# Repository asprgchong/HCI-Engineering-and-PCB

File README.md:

# HCI-Engineering-and-PCB
Project Files from my HCI PCB and HCI Eng classes with Professor Pedro Lopes

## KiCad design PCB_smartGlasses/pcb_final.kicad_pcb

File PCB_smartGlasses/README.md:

## PCB Smart Glasses Project: 
Final Project for HCI PCB with Prof Lopes result

This class was an amazing experience into the harsh world of EE and prototyping. 
My idea was to create smart glasses from scratch that a user would interact with using gestures and a smart glasses product that would also react to the user's environment. 
During the KiCAD wiring and organization process, I had messed up the wiring of the SCL and SDA pins on the wrong pins on the SAMD21 processor which was a TQFP component hot gun soldered down. As depicted above, there is a stray wire running to the VCC pin on my OLED.
There were a lot of things that went wrong with this project and hence it's roughness. But I'm really proud of this project! 

I had no prior experience and I made a fully functioning smart glasses product that allowed the user to see the to-do list. I don't have my glasses anymore, they are with Prof Lopez but I am actively working on my mistakes and trying to make it better.

<p>Components and Schematic Design (Problems in the wiring of the SLA and SCL of the light sensor to the correct pins on the SAMD21- same for the OLED screen)</p>

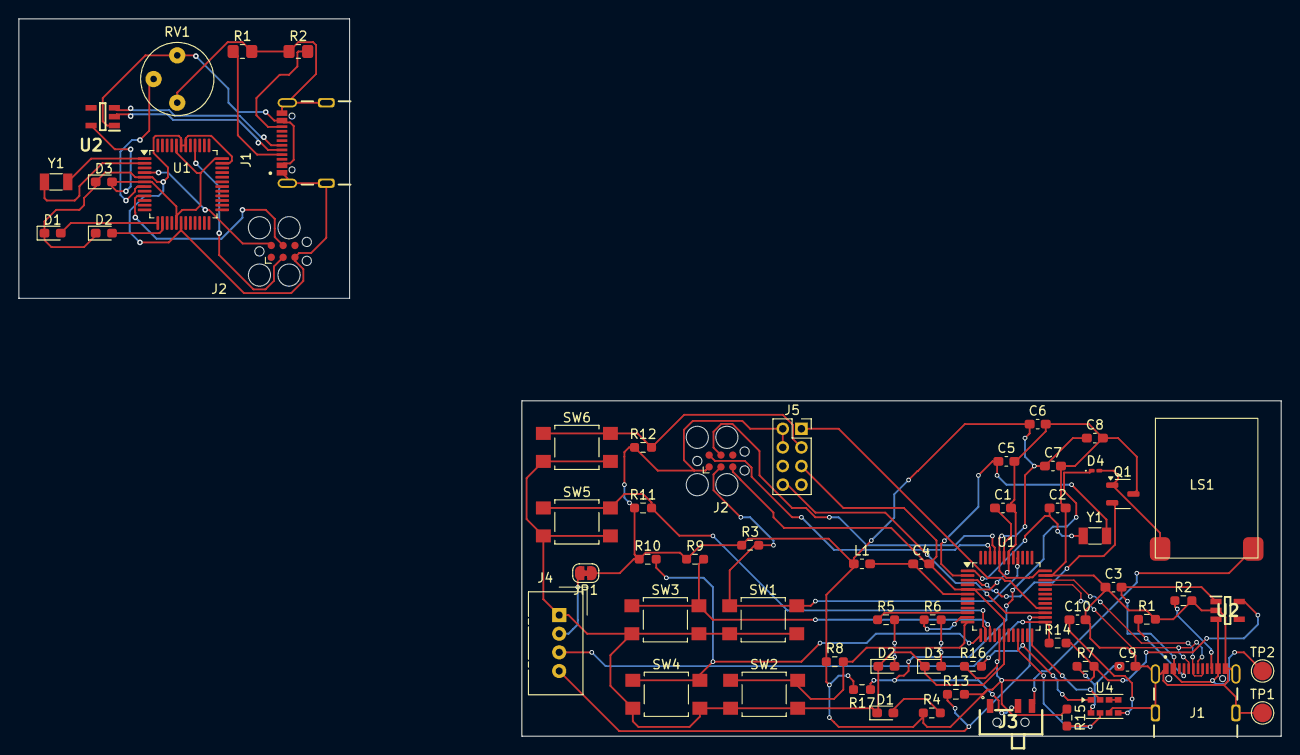
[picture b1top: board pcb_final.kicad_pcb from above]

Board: 2 copper layers, 135.5 x 77.0 mm, 63 parts (0 on the bottom side), 13 nets.

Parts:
C1, C4, C6, C7: 0.1uF; C_0603_1608Metric_Pad1.08x0.95mm_HandSolder
C2, C5: 15uF; C_0603_1608Metric_Pad1.08x0.95mm_HandSolder
C3, C8, C9, C10: 1uF; C_0603_1608Metric_Pad1.08x0.95mm_HandSolder
D1: GREEN; LED_0603_1608Metric_Pad1.05x0.95mm_HandSolder
D1#2, D2#2, D3: LED; LED_0603_1608Metric_Pad1.05x0.95mm_HandSolder
D2, D3#2: RED; LED_0603_1608Metric_Pad1.05x0.95mm_HandSolder
D4: LED_Small; D_0201_0603Metric_Pad0.64x0.40mm_HandSolder
J1, J1#2: USB4105-GF-A; GCT_USB4105-GF-A
J2: SWD_TAG-CONNECT; Tag-Connect_TC2030-IDC-FP_2x03_P1.27mm_Vertical
J2#2: TAG-CONNECT; Tag-Connect_TC2030-IDC-FP_2x03_P1.27mm_Vertical
J3: SSSS810701
J4: Conn_01x04_Socket; NS-Tech_Grove_1x04_P2mm_Vertical
J5: Conn_02x04_Top_Bottom; PinSocket_2x04_P2.00mm_Vertical
JP1: Jumper_2_Bridged; SolderJumper-2_P1.3mm_Bridged_RoundedPad1.0x1.5mm
L1: FB-30R; L_0603_1608Metric_Pad1.05x0.95mm_HandSolder
LS1: OWS-111535LA-8H
Q1: NMOS; SOT-23-3
R1, R2: 5.1k; R_0603_1608Metric_Pad0.98x0.95mm_HandSolder
R1#2, R2#2: 5.1k; R_0805_2012Metric_Pad1.20x1.40mm_HandSolder
R3, R8, R9, R10, R11, R12, R13, R14, R15, R16, R17: 10k; R_0603_1608Metric_Pad0.98x0.95mm_HandSolder
R4, R5, R6: 1k; R_0603_1608Metric_Pad0.98x0.95mm_HandSolder
R7: 22; R_0603_1608Metric_Pad0.98x0.95mm_HandSolder
RV1: R_Potentiometer; Potentiometer_Bourns_3339P_Vertical_HandSoldering
SW1, SW2, SW3, SW4, SW5, SW6: SW_Push; SW_SPST_TL3305A
TP1, TP2: GND_Test; TestPoint_Pad_D2.0mm
U1, U1#2: ATSAMD21G18A-A; TQFP-48_7x7mm_P0.5mm
U2, U2#2: TLV73333PQDBVRQ1; SOT95P280X145-5N
U4: APDS-9960; Avago_APDS-9960
Y1: Crystal_Small; Crystal_SMD_3215-2Pin_3.2x1.5mm
Y1#2: Crystal; Crystal_SMD_3215-2Pin_3.2x1.5mm

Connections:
+5V: J1.A4_B9 (VBUS), J1.B4_A9 (VBUS), RV1.3, U2#2.1 (IN)
/D+: J1.A6 (DP1), J1#2.A6 (DP1), J1#2.B6 (DP2), U1#2.34 (PA25), U2#2.3 (EN)
/D-: J1.B7 (DN2), J1#2.A7 (DN1), J1#2.B7 (DN2), U1#2.33 (PA24), U2#2.2 (GND)
/InCrystal: U1.1 (PA00), Y1#2.1
/OutCrystal: U1.2 (PA01), Y1#2.2
/SWC: J2.4 (SWCLK), J2#2.4 (SWCLK), U1.9 (PA04), U1#2.45 (PA30)
/SWD: J2.2 (SWDIO), J2#2.2 (SWDIO), U1.4 (PA03), U1#2.46 (PA31)
/ledOne: D1#2.2 (A), U1.13 (PA08)
/ledTwo: D2#2.2 (A), U1.14 (PA09)
/pot_pin: RV1.2, U1.7 (PB08)
/regV: D3.2 (A), J2#2.1 (Vref), U1.6 (VDDANA), U1.17 (VDDIO), U1.36 (VDDIO), U1.44 (VDDIN), U2#2.5 (OUT)
/~RST: J2.3 (~RST), J2#2.3 (~RST), R3.2, SW1.1, U1.40 (~RESET), U1#2.40 (~RESET)
GND: C1.2, C2.2, C3.1, C4.2, C5.2, C6.2, C7.2, C8.2, C9.2, C10.2, D1.1 (K), D1#2.1 (K), D2.1 (K), D2#2.1 (K), D3.1 (K), D3#2.1 (K), J1.A1_B12 (GND), J1.B1_A12 (GND), J1.SH1 (SHELL_GND), J1.SH2 (SHELL_GND), J1.SH3 (SHELL_GND), J1.SH4 (SHELL_GND), J1#2.A1_B12 (GND), J1#2.B1_A12 (GND), J1#2.SH1 (SHELL_GND), J1#2.SH2 (SHELL_GND), J1#2.SH3 (SHELL_GND), J1#2.SH4 (SHELL_GND), J2.5 (GND), J2#2.5 (GND), J4.1, J5.5, Q1.3 (S), R1.2, R1#2.2, R2.2, R2#2.1, RV1.1, SW1.2, SW2.2, SW3.2, SW4.2, SW5.2, SW6.2, TP1.1, U1.5 (GNDANA), U1.18 (GND), U1.35 (GND), U1.42 (GND), U1.43 (VDDCORE), U1#2.5 (GNDANA), U1#2.18 (GND), U1#2.35 (GND), U1#2.42 (GND), U2.2 (GND), U4.6 (GND)

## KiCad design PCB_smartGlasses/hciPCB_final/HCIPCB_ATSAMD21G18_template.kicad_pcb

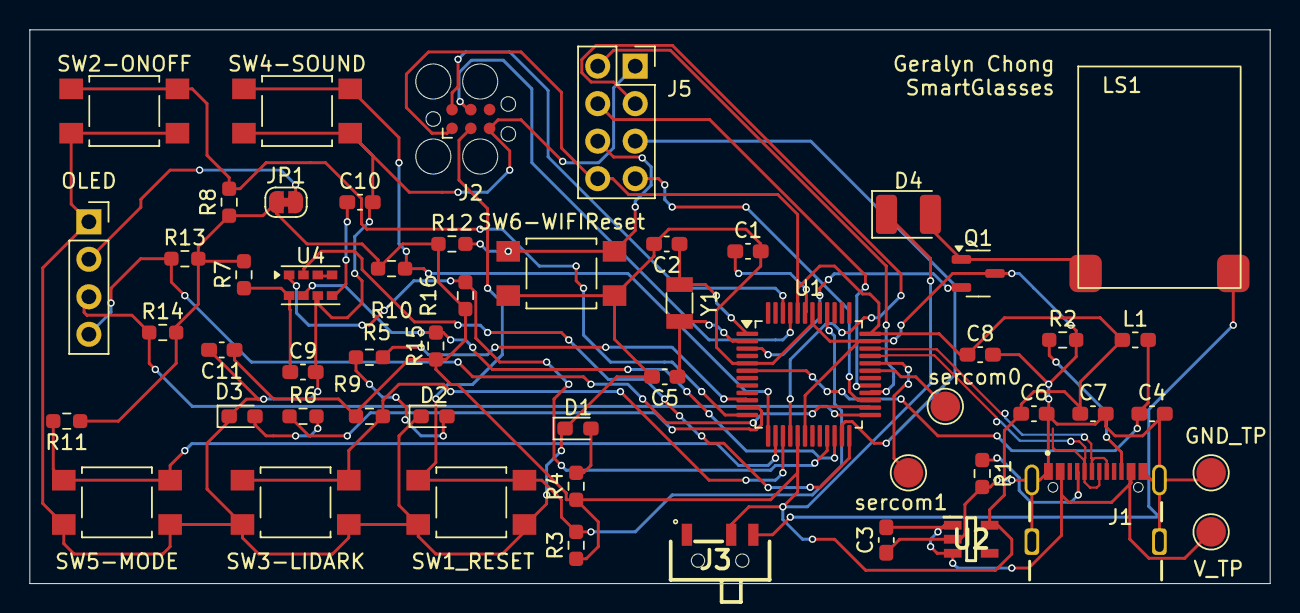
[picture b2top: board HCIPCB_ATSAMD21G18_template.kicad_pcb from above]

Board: 2 copper layers, 84.0 x 37.5 mm, 54 parts (0 on the bottom side), 43 nets.

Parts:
C1, C4, C6, C7: 0.1uF; C_0603_1608Metric_Pad1.08x0.95mm_HandSolder
C2, C5: 15uF; C_0603_1608Metric_Pad1.08x0.95mm_HandSolder
C3, C8, C9, C10: 1uF; C_0603_1608Metric_Pad1.08x0.95mm_HandSolder
C11: 10uF; C_0603_1608Metric_Pad1.08x0.95mm_HandSolder
D1: GREEN; LED_0603_1608Metric_Pad1.05x0.95mm_HandSolder
D2, D3: RED; LED_0603_1608Metric_Pad1.05x0.95mm_HandSolder
D4: DIODE; D_1210_3225Metric_Pad1.42x2.65mm_HandSolder
GND_TP: GND_Test; TestPoint_Pad_D2.0mm
J1: USB4105-GF-A; GCT_USB4105-GF-A
J2: SWD_TAG-CONNECT; Tag-Connect_TC2030-IDC-FP_2x03_P1.27mm_Vertical
J3: SSSS810701
J5: Conn_02x04_Top_Bottom; PinSocket_2x04_P2.54mm_Vertical
JP1: Jumper_2_Bridged; SolderJumper-2_P1.3mm_Bridged_RoundedPad1.0x1.5mm
L1: FB-30R; L_0603_1608Metric_Pad1.05x0.95mm_HandSolder
LS1: OWS-111535LA-8H
OLED: OLED; PinSocket_1x04_P2.54mm_Vertical
Q1: NMOS; SOT-23-3
R1, R2: 5.1k; R_0603_1608Metric_Pad0.98x0.95mm_HandSolder
R3, R8, R9, R10, R11, R12: 10k; R_0603_1608Metric_Pad0.98x0.95mm_HandSolder
R4, R5, R6: 1k; R_0603_1608Metric_Pad0.98x0.95mm_HandSolder
R7: 22; R_0603_1608Metric_Pad0.98x0.95mm_HandSolder
R13, R14, R15, R16: 4.7k; R_0603_1608Metric_Pad0.98x0.95mm_HandSolder
SW1_RESET, SW2-ONOFF, SW3-LIDARK, SW4-SOUND, SW5-MODE, SW6-WIFIReset: SW_Push; SW_SPST_TL3305A
U1: ATSAMD21G18A-A; TQFP-48_7x7mm_P0.5mm
U2: TLV73333PQDBVRQ1; SOT95P280X145-5N
U4: APDS-9960; Avago_APDS-9960
V_TP: GND_Test; TestPoint_Pad_D2.0mm
Y1: Crystal_Small; Crystal_SMD_3215-2Pin_3.2x1.5mm
sercom0: sercom[0]; TestPoint_Pad_D2.0mm
sercom1: sercom[1]; TestPoint_Pad_D2.0mm

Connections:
+3V3: C6.1, C7.1, C8.1, C11.1, D4.1 (K), J2.1 (Vref), J3.2, J5.8, JP1.1 (A), L1.1, R3.1, R4.1, R7.2, R8.1, R9.1, R10.1, R11.1, R12.1, R13.2, R14.2, R15.1, R16.1, U1.17 (VDDIO), U1.36 (VDDIO), U1.44 (VDDIN), U2.5 (OUT)
/Button_LiDark: R9.2, SW3-LIDARK.1, U1.15 (PA10)
/Button_MODE: R11.2, SW5-MODE.1, U1.14 (PA09)
/Button_ONOFF: R8.2, SW2-ONOFF.1, U1.12 (PA07)
/Button_sound: R10.2, SW4-SOUND.1, U1.13 (PA08)
/CHPD: J5.4, U1.29 (PA20)
/D+: J1.A6 (DP1), J1.B6 (DP2), U1.34 (PA25)
/D-: J1.A7 (DN1), J1.B7 (DN2), U1.33 (PA24)
/GPIO0: J5.5, U1.23 (PA14)
/GPIO2: J5.3, U1.16 (PA11)
/LED1: R5.1, U1.10 (PA05)
/LED2: R6.1, U1.11 (PA06)
/LED_A: C10.1, U4.5 (LED_A)
/LightSCL: R15.2, U1.22 (PA13), U4.7 (SCL)
/LightSDA: R16.2, U1.21 (PA12), U4.1 (SDA)
/OLED_SCL: OLED.3, R14.1, U1.25 (PA16)
/OLED_SDA: OLED.4, R13.1, U1.26 (PA17)
/RST: J5.6, R12.2, SW6-WIFIReset.1
/RXI: J5.7, U1.27 (PA18)
/SPK1: Q1.2 (G), U1.3 (PA02)
/SWC: J2.4 (SWCLK), U1.45 (PA30)
/SWD: J2.2 (SWDIO), U1.46 (PA31)
/TXO: J5.2, U1.28 (PA19)
/VDDANA: C4.1, L1.2, U1.6 (VDDANA)
/XC1: C2.1, U1.1 (PA00), Y1.2
/XC2: C5.1, U1.2 (PA01), Y1.1
/ex-interrupt: U1.24 (PA15), U4.2 (INT)
/~RST: J2.3 (~RST), R3.2, SW1_RESET.1, U1.40 (~RESET)
GND: C1.2, C2.2, C3.1, C4.2, C5.2, C6.2, C7.2, C8.2, C9.2, C10.2, C11.2, D1.1 (K), D2.1 (K), D3.1 (K), GND_TP.1, J1.A1_B12 (GND), J1.B1_A12 (GND), J1.SH1 (SHELL_GND), J1.SH2 (SHELL_GND), J1.SH3 (SHELL_GND), J1.SH4 (SHELL_GND), J2.5 (GND), J5.1, OLED.1, Q1.3 (S), R1.2, R2.2, SW1_RESET.2, SW2-ONOFF.2, SW3-LIDARK.2, SW4-SOUND.2, SW5-MODE.2, SW6-WIFIReset.2, U1.5 (GNDANA), U1.18 (GND), U1.35 (GND), U1.42 (GND), U2.2 (GND), U4.6 (GND)
unnamed: D1.2 (A), R4.2
unnamed: D2.2 (A), R5.2
unnamed: D3.2 (A), R6.2
unnamed: D4.2 (A), LS1.2, Q1.1 (D)
unnamed: J1.A5 (CC1), R1.1
unnamed: J1.B5 (CC2), R2.1
unnamed: J3.3, LS1.1
unnamed: JP1.2 (B), OLED.2
unnamed: U1.31 (PA22), sercom0.1
unnamed: U1.32 (PA23), sercom1.1
unnamed: C1.1, U1.43 (VDDCORE)
unnamed: U4.3 (LDR), U4.4 (LED_K)
unnamed: C9.1, R7.1, U4.8 (VDD)
VBUS: C3.2, J1.A4_B9 (VBUS), J1.B4_A9 (VBUS), U2.1 (IN), U2.3 (EN), V_TP.1

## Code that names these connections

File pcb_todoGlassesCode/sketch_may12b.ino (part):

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#include <OneButton.h>

// Button Pins 
// PA07 - 9 - ONOFF Button - Digital High 
// PA08 - 4 - SOUND - Digital Low 
// PA09 - 3 - MODE - Digital Low
// PA10 - 1 - LIDARK - Digital Low
// #define ADD_TODO 9
// #define REMOVE_TODO 4
// #define TIMER_PAUSE 3
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
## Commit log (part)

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2024-12-25 3D print designs, Gerber files for PCB, and code
2024-12-25 clear
2024-12-25 HCI Eng folder
2024-12-25 PCB folder
